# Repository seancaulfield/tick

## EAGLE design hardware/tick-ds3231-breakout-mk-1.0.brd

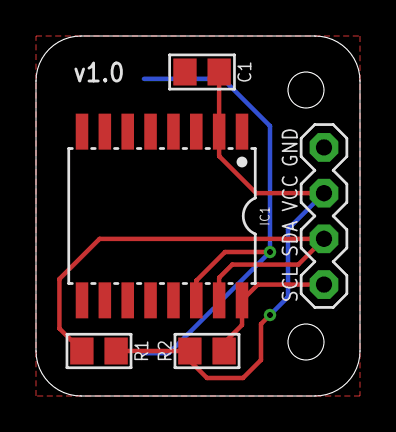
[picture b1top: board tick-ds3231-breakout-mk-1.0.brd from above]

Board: 2 copper layers, 18.0 x 20.0 mm, 7 parts (1 on the bottom side), 5 nets.

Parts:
C1: 100n; C0805
FRAME1: FRAME-LETTERNO_PACKAGE; DUMMY
I2C: M04-I2CPTH-0.1IN-CENTERED; 1X04-PTH-VERT-I2C-CENTERED
IC1: DS3231; SO16W
R1, R2: 4.7k; R0805
RTC_BATT: CR1225; BATTCON_12MM_SMD

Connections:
GND: C1.2, I2C.GND, IC1.5, IC1.6, IC1.7, IC1.8, IC1.9, IC1.10, IC1.11, IC1.12, IC1.13, RTC_BATT.-
SCL: I2C.SCL, IC1.16, R2.2
SDA: I2C.SDA, IC1.15, R1.2
VBAT: IC1.14, RTC_BATT.+@1, RTC_BATT.+@2
VCC: C1.1, I2C.VCC, IC1.2, R1.1, R2.1

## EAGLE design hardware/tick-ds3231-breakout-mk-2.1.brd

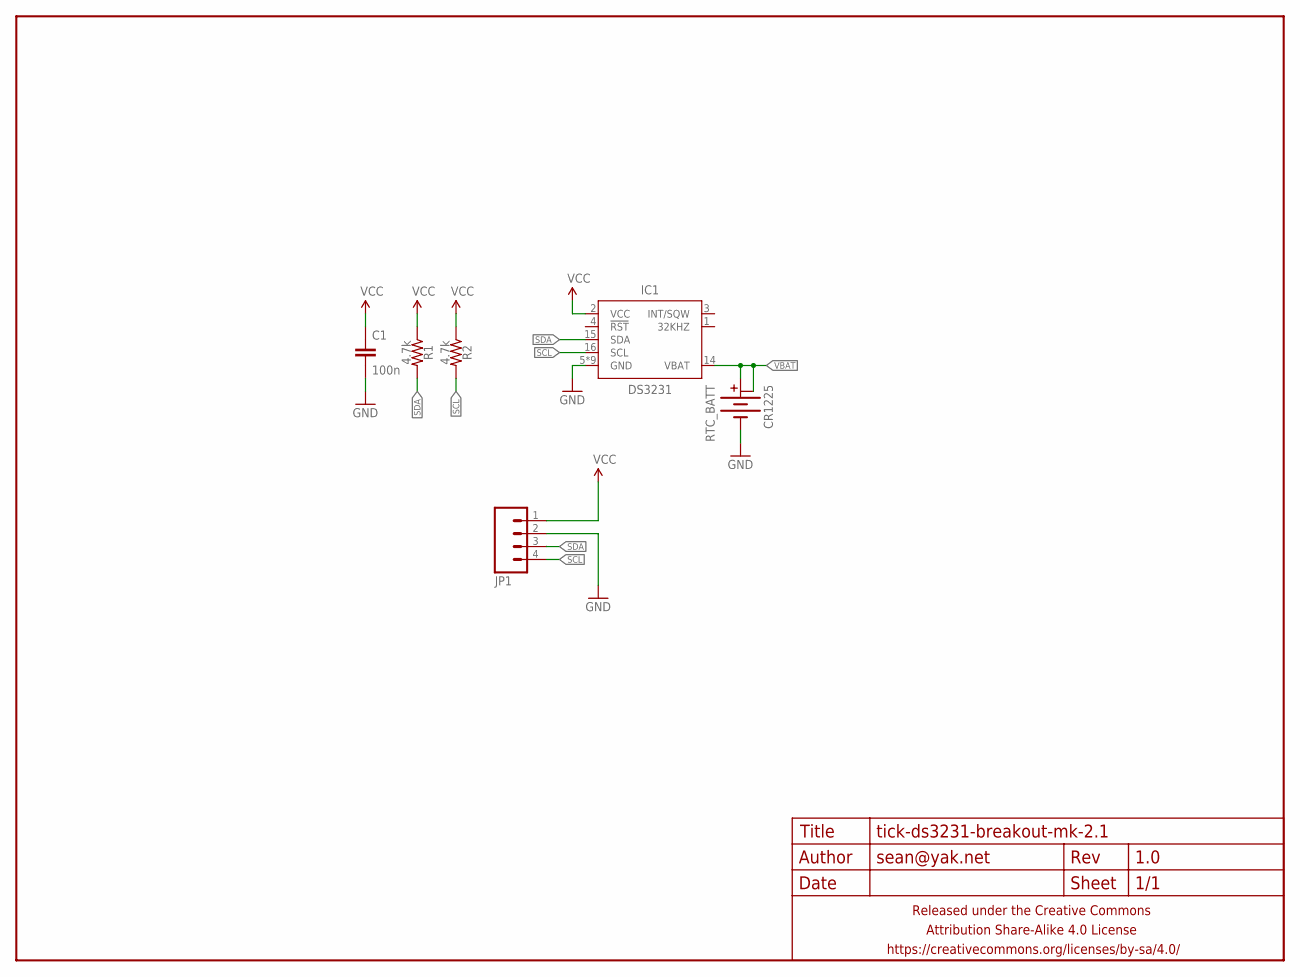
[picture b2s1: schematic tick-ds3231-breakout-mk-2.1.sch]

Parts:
C1: 100n; C0805
FRAME1: FRAME-LETTERNO_PACKAGE; DUMMY
IC1: DS3231; SO16W
JP1: M04PTH; 1X04-PTH-VERT
R1, R2: 4.7k; R0805
RTC_BATT: CR1225; BATTCON_12MM_SMD

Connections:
GND: C1.2, IC1.5 (GND), IC1.6 (GND), IC1.7 (GND), IC1.8 (GND), IC1.9 (GND), IC1.10 (GND), IC1.11 (GND), IC1.12 (GND), IC1.13 (GND), JP1.2, RTC_BATT.-
SCL: IC1.16 (SCL), JP1.4, R2.2
SDA: IC1.15 (SDA), JP1.3, R1.2
VBAT: IC1.14 (VBAT), RTC_BATT.+@1 (+), RTC_BATT.+@2 (+1)
VCC: C1.1, IC1.2 (VCC), JP1.1, R1.1, R2.1

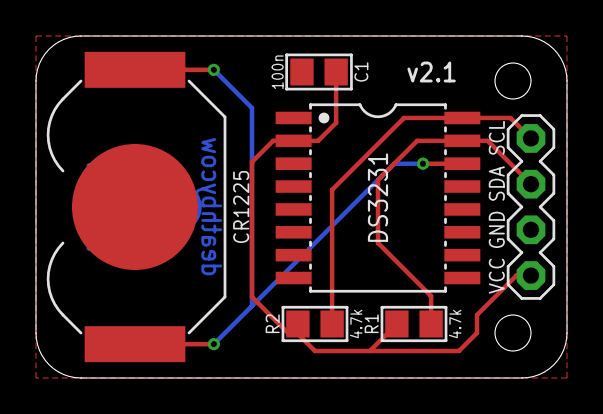
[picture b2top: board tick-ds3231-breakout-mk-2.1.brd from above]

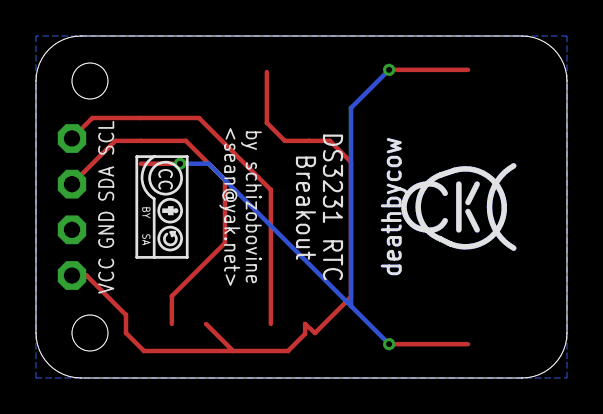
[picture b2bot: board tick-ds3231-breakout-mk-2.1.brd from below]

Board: 2 copper layers, 29.5 x 19.0 mm, 9 parts (2 on the bottom side), 5 nets.

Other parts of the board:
U$1: COW_SMALL_METAL
U$2: CC-BY-SA-4.0-NO-URL

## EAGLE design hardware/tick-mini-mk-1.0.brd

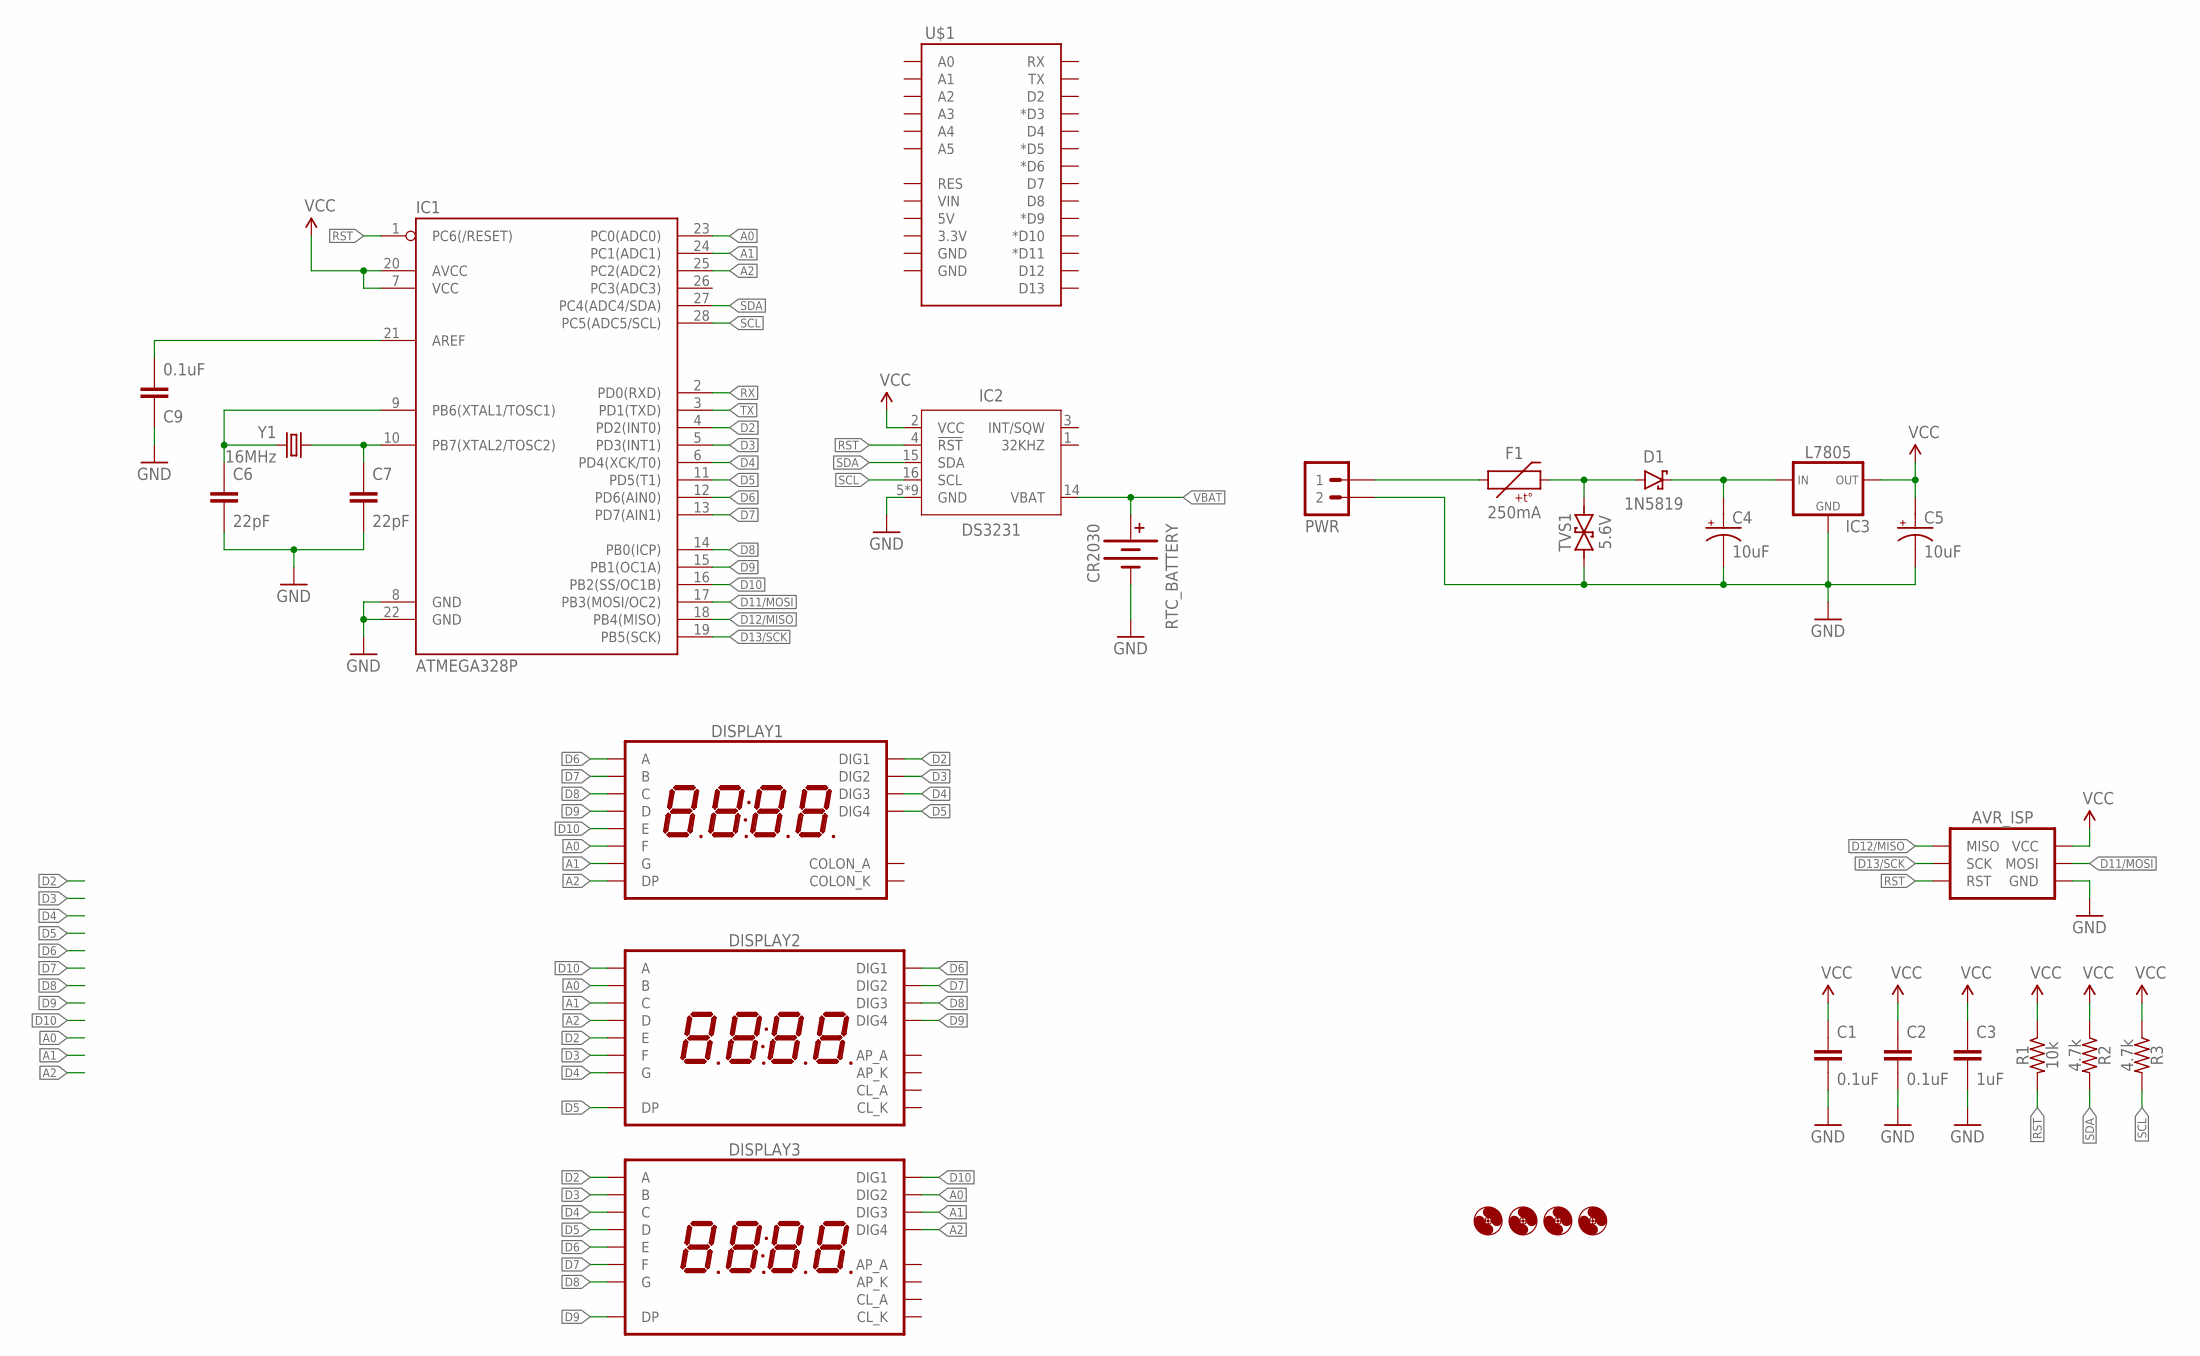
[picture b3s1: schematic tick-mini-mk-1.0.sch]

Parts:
AVR_ISP: AVR_SPI_PRG_6PTH; 2X3
C1, C2, C9: 0.1uF; C025-024X044
C3: 1uF; C025-024X044
C4, C5: 10uF; E2-5
C6, C7: 22pF; C025-024X044
D1: 1N5819; DIODE-10.16MM
DISPLAY1: 7SEG_4DIGIT_COLON14.2MM-CC; 7SEG_4DIG_0.56IN_14MM_ADAFRUIT
DISPLAY2, DISPLAY3: 7SEG_4DIGIT_COLON_APOS; 7SEG_4DIG_10MM
F1: 250mA; PTC-PTH-5.08MM
H1, H2, H3, H4: HOLE#2; HOLE-#2
IC1: ATMEGA328P; DIL28-3
IC2: DS3231; SO16W
IC3: L7805; TO-92-AMMO
PWR: M02JST-PTH-VERT; JST-2-PH-VERT-PTH
R1: 10k; RESISTOR-AXIAL-PTH-7.62MM
R2, R3: 4.7k; RESISTOR-AXIAL-PTH-6.35MM
RTC_BATTERY: CR2030; BATTCON_12MM
TVS1: 5.6V; DO-41-TVS-BI-10.16MM
U$1: ARDUINO_SHIELD_SMALLER; ARDUINO_SHIELD_NOOUTLINE_INSIDE_SMALLER
Y1: 16MHz; HC49U-V

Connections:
A0: DISPLAY1.P$12 (F), DISPLAY2.16 (B), DISPLAY3.2 (DIG2), IC1.23 (PC0(ADC0))
A1: DISPLAY1.P$5 (G), DISPLAY2.13 (C), DISPLAY3.6 (DIG3), IC1.24 (PC1(ADC1))
A2: DISPLAY1.P$3 (DP), DISPLAY2.3 (D), DISPLAY3.8 (DIG4), IC1.25 (PC2(ADC2))
D2: DISPLAY1.P$14 (DIG1), DISPLAY2.5 (E), DISPLAY3.14 (A), IC1.4 (PD2(INT0))
D3: DISPLAY1.P$11 (DIG2), DISPLAY2.11 (F), DISPLAY3.16 (B), IC1.5 (PD3(INT1))
D4: DISPLAY1.P$10 (DIG3), DISPLAY2.15 (G), DISPLAY3.13 (C), IC1.6 (PD4(XCK/T0))
D5: DISPLAY1.P$6 (DIG4), DISPLAY2.7 (DP), DISPLAY3.3 (D), IC1.11 (PD5(T1))
D6: DISPLAY1.P$13 (A), DISPLAY2.1 (DIG1), DISPLAY3.5 (E), IC1.12 (PD6(AIN0))
D7: DISPLAY1.P$9 (B), DISPLAY2.2 (DIG2), DISPLAY3.11 (F), IC1.13 (PD7(AIN1))
D8: DISPLAY1.P$4 (C), DISPLAY2.6 (DIG3), DISPLAY3.15 (G), IC1.14 (PB0(ICP))
D9: DISPLAY1.P$2 (D), DISPLAY2.8 (DIG4), DISPLAY3.7 (DP), IC1.15 (PB1(OC1A))
D10: DISPLAY1.P$1 (E), DISPLAY2.14 (A), DISPLAY3.1 (DIG1), IC1.16 (PB2(SS/OC1B))
D11/MOSI: AVR_ISP.4 (MOSI), IC1.17 (PB3(MOSI/OC2))
D12/MISO: AVR_ISP.1 (MISO), IC1.18 (PB4(MISO))
D13/SCK: AVR_ISP.3 (SCK), IC1.19 (PB5(SCK))
GND: AVR_ISP.6 (GND), C1.2, C2.2, C3.2, C4.-, C5.-, C6.2, C7.2, C9.1, IC1.8 (GND), IC1.22 (GND), IC2.5 (GND), IC2.6 (GND), IC2.7 (GND), IC2.8 (GND), IC2.9 (GND), IC2.10 (GND), IC2.11 (GND), IC2.12 (GND), IC2.13 (GND), IC3.2 (GND), PWR.2, RTC_BATTERY.GND (-), TVS1.P$1 (1)
unnamed: C9.2, IC1.21 (AREF)
unnamed: D1.A, F1.P$2 (2), TVS1.P$2 (2)
unnamed: C6.1, IC1.9 (PB6(XTAL1/TOSC1)), Y1.2
unnamed: F1.P$1 (1), PWR.1
unnamed: C4.+, D1.C, IC3.1 (IN)
unnamed: C7.1, IC1.10 (PB7(XTAL2/TOSC2)), Y1.1
RST: AVR_ISP.5 (RST), IC1.1 (PC6(/RESET)), IC2.4 (!RST), R1.P$2 (2)
RX: IC1.2 (PD0(RXD))
SCL: IC1.28 (PC5(ADC5/SCL)), IC2.16 (SCL), R3.P$2 (2)
SDA: IC1.27 (PC4(ADC4/SDA)), IC2.15 (SDA), R2.P$2 (2)
TX: IC1.3 (PD1(TXD))
VBAT: IC2.14 (VBAT), RTC_BATTERY.PWR@1 (+)
VCC: AVR_ISP.2 (VCC), C1.1, C2.1, C3.1, C5.+, IC1.7 (VCC), IC1.20 (AVCC), IC2.2 (VCC), IC3.3 (OUT), R1.P$1 (1), R2.P$1 (1), R3.P$1 (1)

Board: 2 copper layers, 29 parts (5 on the bottom side), 27 nets, no tracks yet.

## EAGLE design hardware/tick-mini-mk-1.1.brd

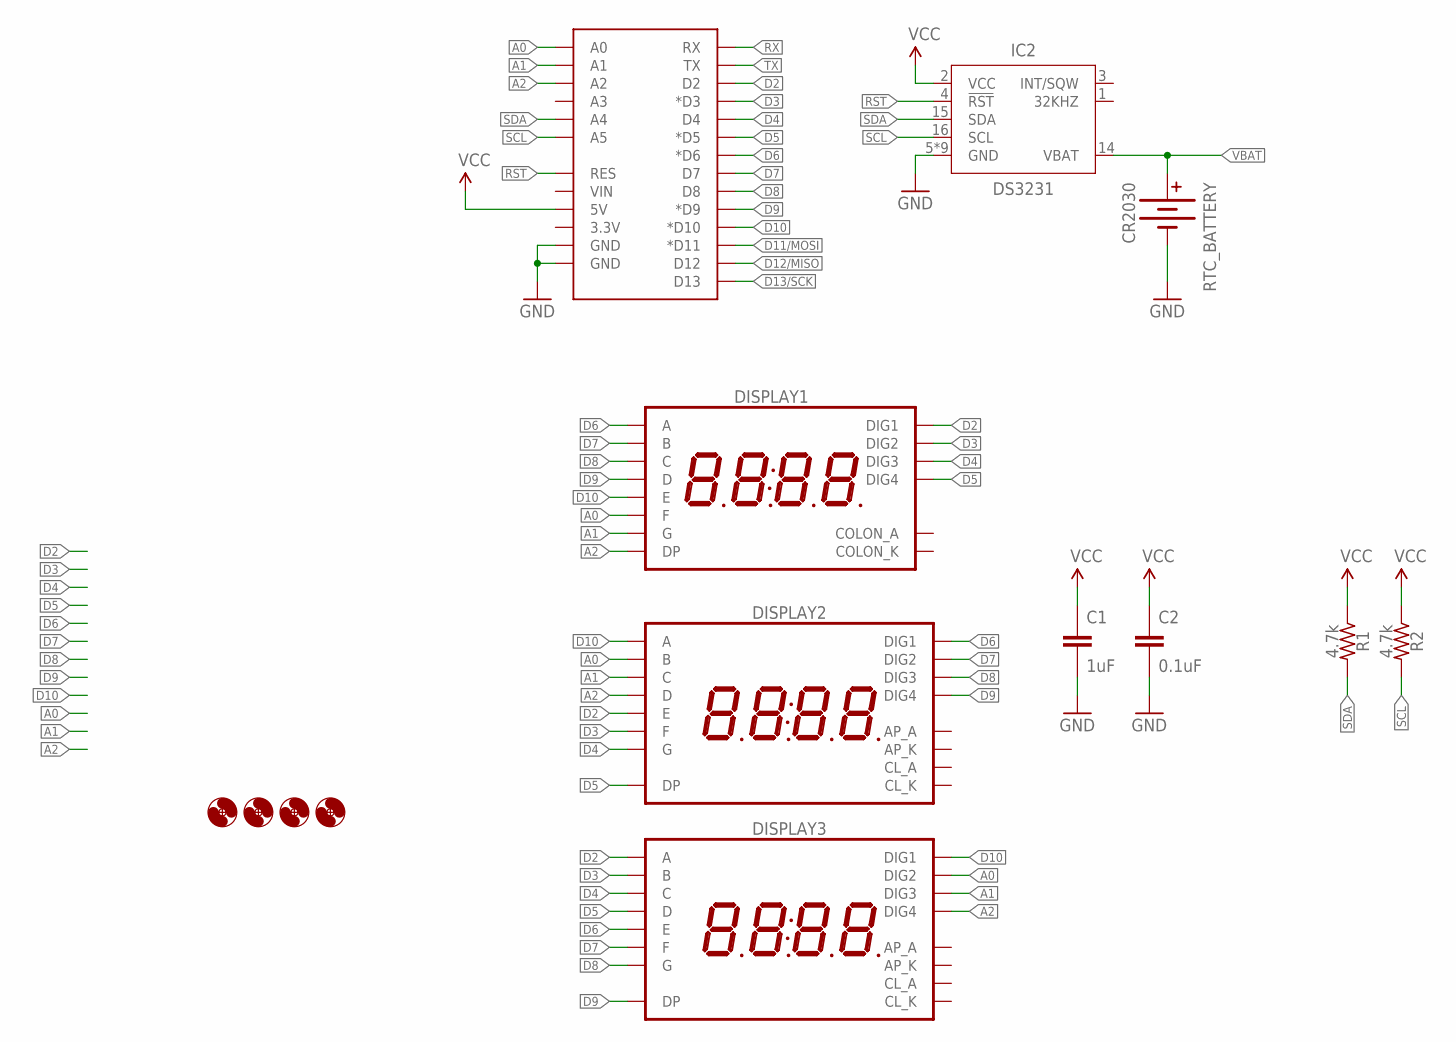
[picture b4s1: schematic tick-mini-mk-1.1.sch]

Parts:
C1: 1uF; C025-024X044
C2: 0.1uF; C025-024X044
DISPLAY1: 7SEG_4DIGIT_COLON14.2MM-CC-NS; 7SEG_4DIG_NS
DISPLAY2, DISPLAY3: 7SEG_4DIGIT_COLON_APOS; 7SEG_4DIG_10MM
H1, H2, H3, H4: HOLE#2; HOLE-#2
IC2: DS3231; SO16W
R1, R2: 4.7k; RESISTOR-AXIAL-PTH-6.35MM
RTC_BATTERY: CR2030; BATTCON_20MM_MINE
U$1: ARDUINO_SHIELD_SMALLER; ARDUINO_SHIELD_NOOUTLINE_INSIDE_SMALLER

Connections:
A0: DISPLAY1.P$12 (F), DISPLAY2.16 (B), DISPLAY3.2 (DIG2), U$1.A0
A1: DISPLAY1.P$5 (G), DISPLAY2.13 (C), DISPLAY3.6 (DIG3), U$1.A1
A2: DISPLAY1.P$3 (DP), DISPLAY2.3 (D), DISPLAY3.8 (DIG4), U$1.A2
D2: DISPLAY1.P$14 (DIG1), DISPLAY2.5 (E), DISPLAY3.14 (A), U$1.D2
D3: DISPLAY1.P$11 (DIG2), DISPLAY2.11 (F), DISPLAY3.16 (B), U$1.D3 (*D3)
D4: DISPLAY1.P$10 (DIG3), DISPLAY2.15 (G), DISPLAY3.13 (C), U$1.D4
D5: DISPLAY1.P$6 (DIG4), DISPLAY2.7 (DP), DISPLAY3.3 (D), U$1.D5 (*D5)
D6: DISPLAY1.P$13 (A), DISPLAY2.1 (DIG1), DISPLAY3.5 (E), U$1.D6 (*D6)
D7: DISPLAY1.P$9 (B), DISPLAY2.2 (DIG2), DISPLAY3.11 (F), U$1.D7
D8: DISPLAY1.P$4 (C), DISPLAY2.6 (DIG3), DISPLAY3.15 (G), U$1.D8
D9: DISPLAY1.P$2 (D), DISPLAY2.8 (DIG4), DISPLAY3.7 (DP), U$1.D9 (*D9)
D10: DISPLAY1.P$1 (E), DISPLAY2.14 (A), DISPLAY3.1 (DIG1), U$1.D10 (*D10)
D11/MOSI: U$1.D11 (*D11)
D12/MISO: U$1.D12
D13/SCK: U$1.D13
GND: C1.2, C2.2, IC2.5 (GND), IC2.6 (GND), IC2.7 (GND), IC2.8 (GND), IC2.9 (GND), IC2.10 (GND), IC2.11 (GND), IC2.12 (GND), IC2.13 (GND), RTC_BATTERY.BOTTOM (-), U$1.GND@0 (GND), U$1.GND@1 (GND)
RST: IC2.4 (!RST), U$1.RES
RX: U$1.RX
SCL: IC2.16 (SCL), R2.P$2 (2), U$1.A5
SDA: IC2.15 (SDA), R1.P$2 (2), U$1.A4
TX: U$1.TX
VBAT: IC2.14 (VBAT), RTC_BATTERY.TOP@1 (+), RTC_BATTERY.TOP@2 (+)
VCC: C1.1, C2.1, IC2.2 (VCC), R1.P$1 (1), R2.P$1 (1), U$1.5V

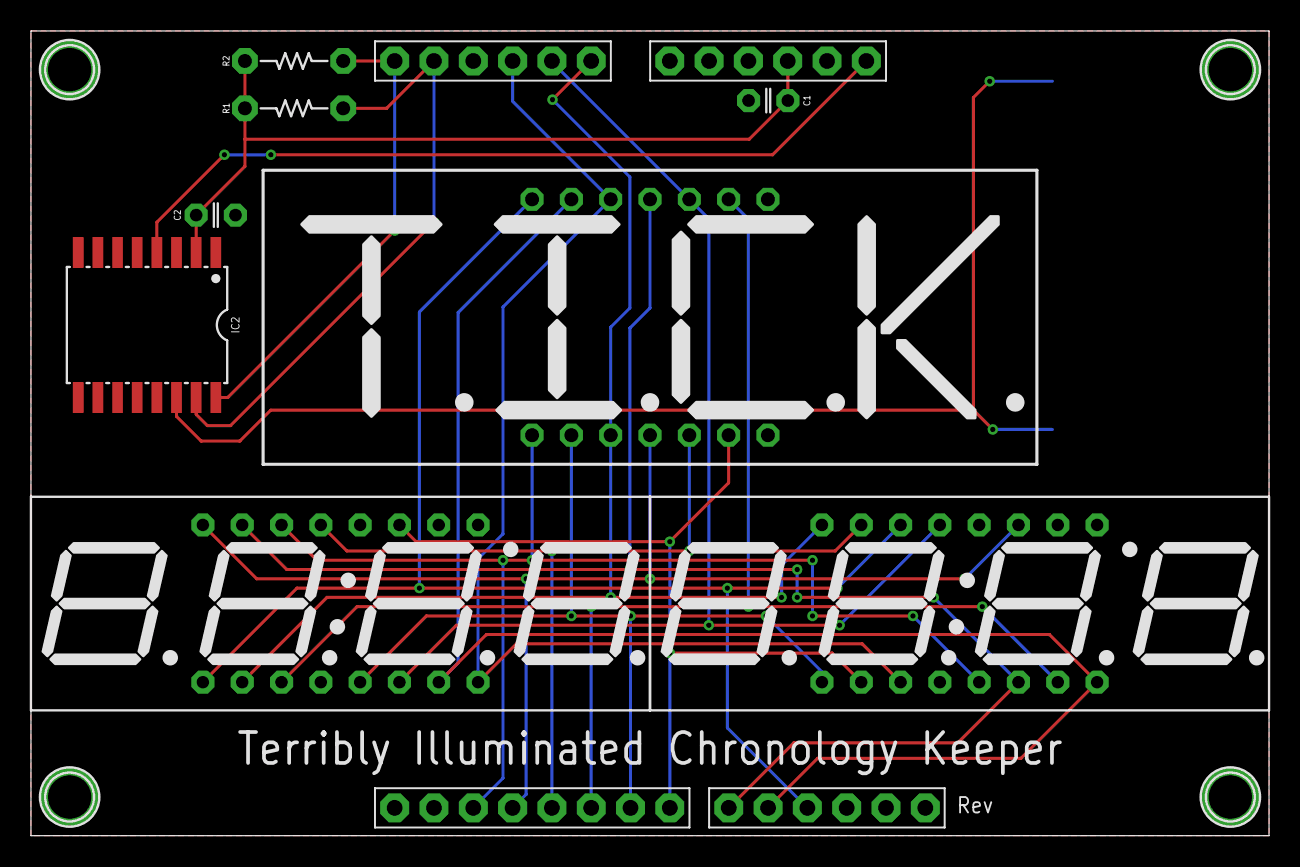
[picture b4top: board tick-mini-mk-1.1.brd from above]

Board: 2 copper layers, 80.0 x 52.0 mm, 15 parts (1 on the bottom side), 18 nets.

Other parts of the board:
U$2: TICK_SYMBOL_0.56

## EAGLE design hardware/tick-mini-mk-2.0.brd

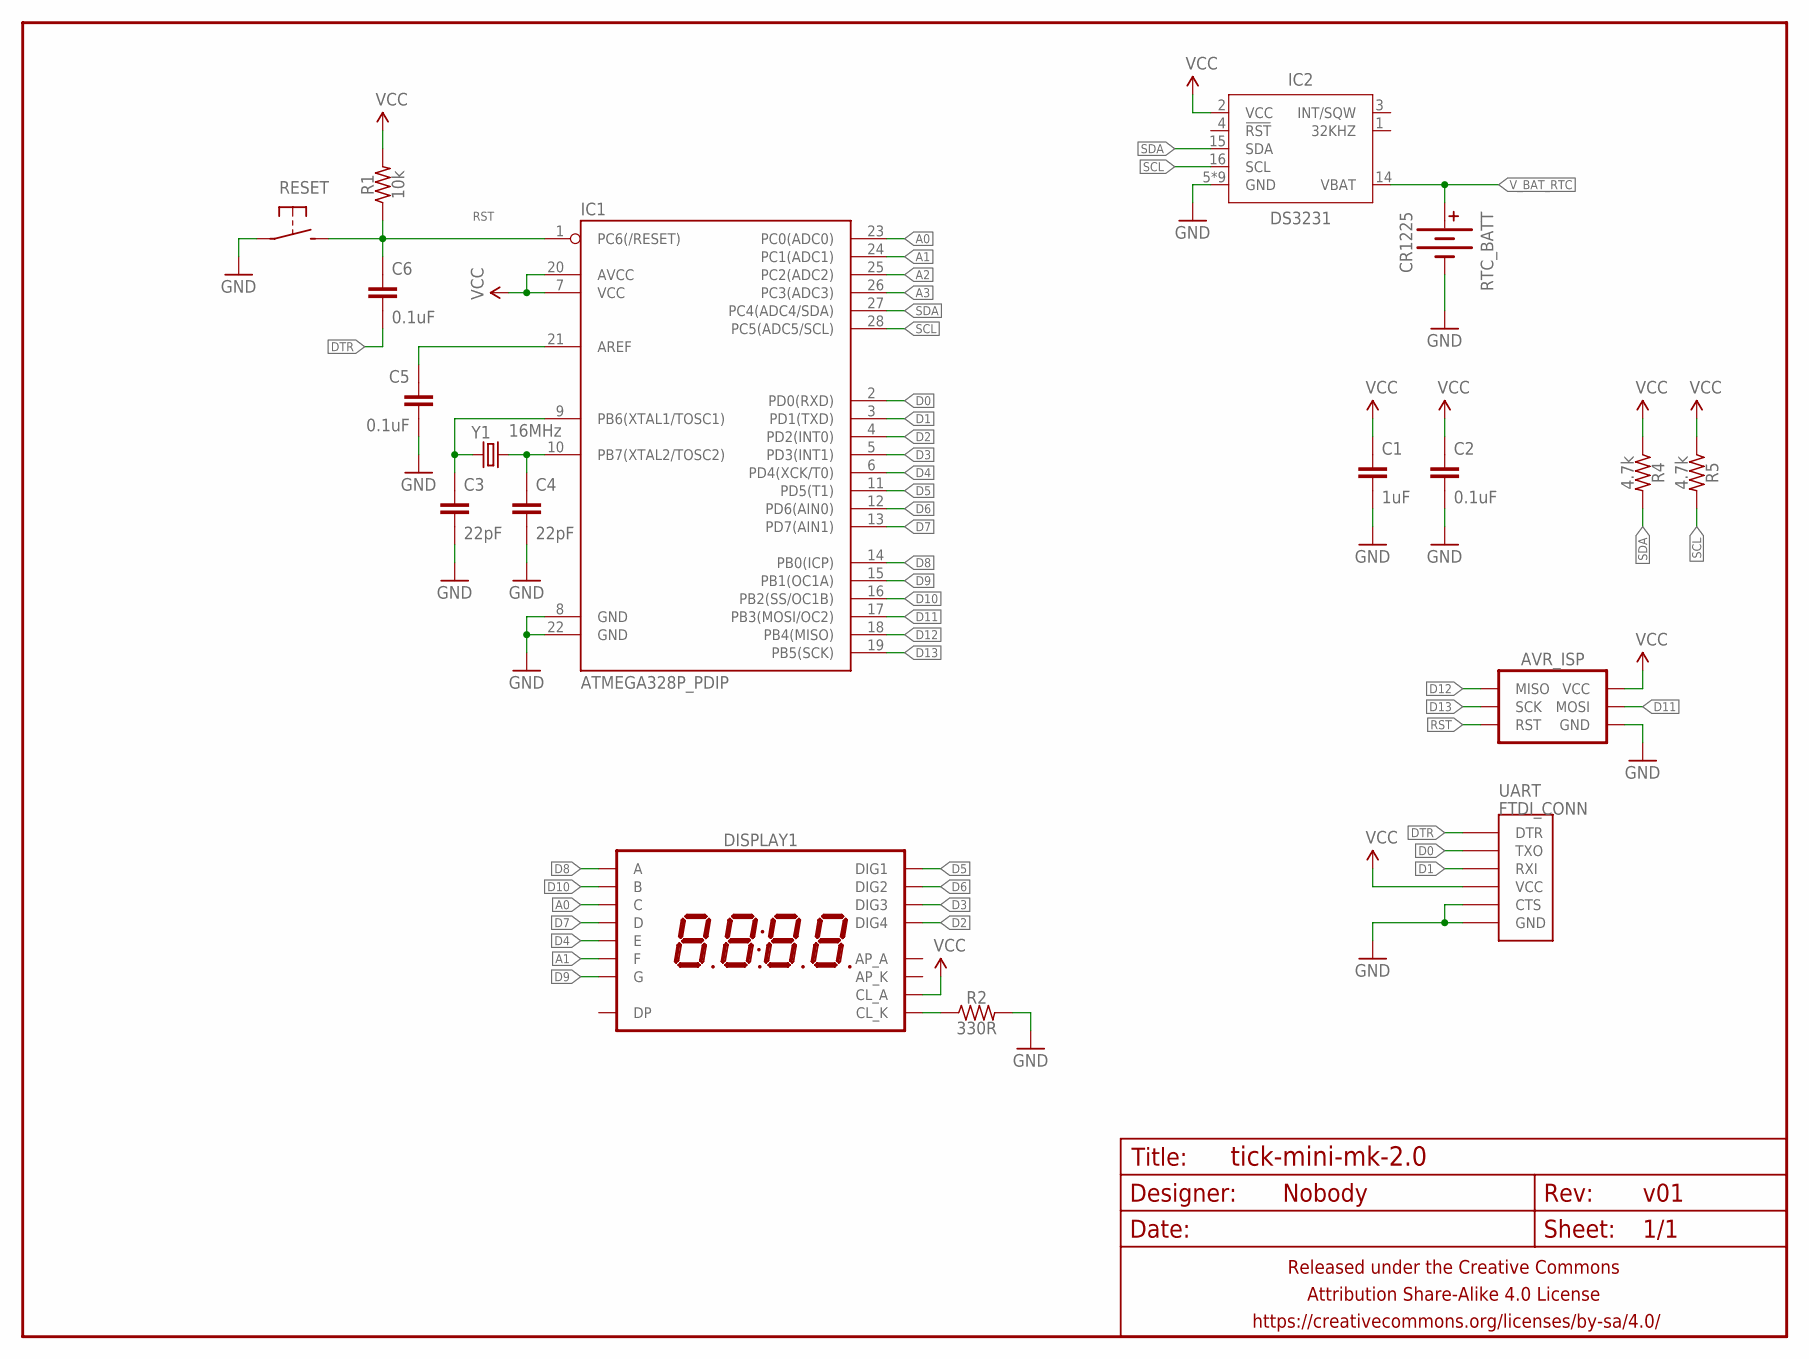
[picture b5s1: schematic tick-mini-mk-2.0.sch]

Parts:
AVR_ISP: AVR_SPI_PRG_6PTH; 2X3
C1: 1uF; C025-024X044
C2, C5, C6: 0.1uF; C025-024X044
C3, C4: 22pF; C025-024X044
DISPLAY1: 7SEG_4DIGIT_COLON_APOS; 7SEG_4DIG_10MM
FRAME1: FRAME-LETTERNO_PACKAGE; DUMMY
IC1: ATMEGA328P_PDIP; DIL28-3
IC2: DS3231; SO16W
R1: 10k; RESISTOR-AXIAL-PTH-6.35MM
R2: 330R; RESISTOR-AXIAL-PTH-6.35MM
R4, R5: 4.7k; RESISTOR-AXIAL-PTH-6.35MM
RESET: SPST-NO-TACT6MM-PTH-SMALL-PADS; DTS-6-SMALL-PADS
RTC_BATT: CR1225; BATTCON_12MM_PTH_TOPLOAD
UART: FTDI_CONN
Y1: 16MHz; HC49U-V

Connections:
A0: DISPLAY1.13 (C), IC1.23 (PC0(ADC0))
A1: DISPLAY1.11 (F), IC1.24 (PC1(ADC1))
A2: IC1.25 (PC2(ADC2))
A3: IC1.26 (PC3(ADC3))
D0: IC1.2 (PD0(RXD)), UART.TXO
D1: IC1.3 (PD1(TXD)), UART.RXI
D2: DISPLAY1.8 (DIG4), IC1.4 (PD2(INT0))
D3: DISPLAY1.6 (DIG3), IC1.5 (PD3(INT1))
D4: DISPLAY1.5 (E), IC1.6 (PD4(XCK/T0))
D5: DISPLAY1.1 (DIG1), IC1.11 (PD5(T1))
D6: DISPLAY1.2 (DIG2), IC1.12 (PD6(AIN0))
D7: DISPLAY1.3 (D), IC1.13 (PD7(AIN1))
D8: DISPLAY1.14 (A), IC1.14 (PB0(ICP))
D9: DISPLAY1.15 (G), IC1.15 (PB1(OC1A))
D10: DISPLAY1.16 (B), IC1.16 (PB2(SS/OC1B))
D11: AVR_ISP.4 (MOSI), IC1.17 (PB3(MOSI/OC2))
D12: AVR_ISP.1 (MISO), IC1.18 (PB4(MISO))
D13: AVR_ISP.3 (SCK), IC1.19 (PB5(SCK))
DTR: C6.2, UART.DTR
GND: AVR_ISP.6 (GND), C1.2, C2.2, C3.2, C4.2, C5.2, IC1.8 (GND), IC1.22 (GND), IC2.5 (GND), IC2.6 (GND), IC2.7 (GND), IC2.8 (GND), IC2.9 (GND), IC2.10 (GND), IC2.11 (GND), IC2.12 (GND), IC2.13 (GND), R2.P$2 (2), RESET.1, RESET.2 (1), RTC_BATT.-, UART.CTS, UART.GND
unnamed: C4.1, IC1.10 (PB7(XTAL2/TOSC2)), Y1.2
unnamed: C3.1, IC1.9 (PB6(XTAL1/TOSC1)), Y1.1
unnamed: C5.1, IC1.21 (AREF)
unnamed: DISPLAY1.12 (CL_K), R2.P$1 (1)
RST: AVR_ISP.5 (RST), C6.1, IC1.1 (PC6(/RESET)), R1.P$1 (1), RESET.3 (2), RESET.4 (2)
SCL: IC1.28 (PC5(ADC5/SCL)), IC2.16 (SCL), R5.P$2 (2)
SDA: IC1.27 (PC4(ADC4/SDA)), IC2.15 (SDA), R4.P$2 (2)
VCC: AVR_ISP.2 (VCC), C1.1, C2.1, DISPLAY1.4 (CL_A), IC1.7 (VCC), IC1.20 (AVCC), IC2.2 (VCC), R1.P$2 (2), R4.P$1 (1), R5.P$1 (1), UART.VCC
V_BAT_RTC: IC2.14 (VBAT), RTC_BATT.+

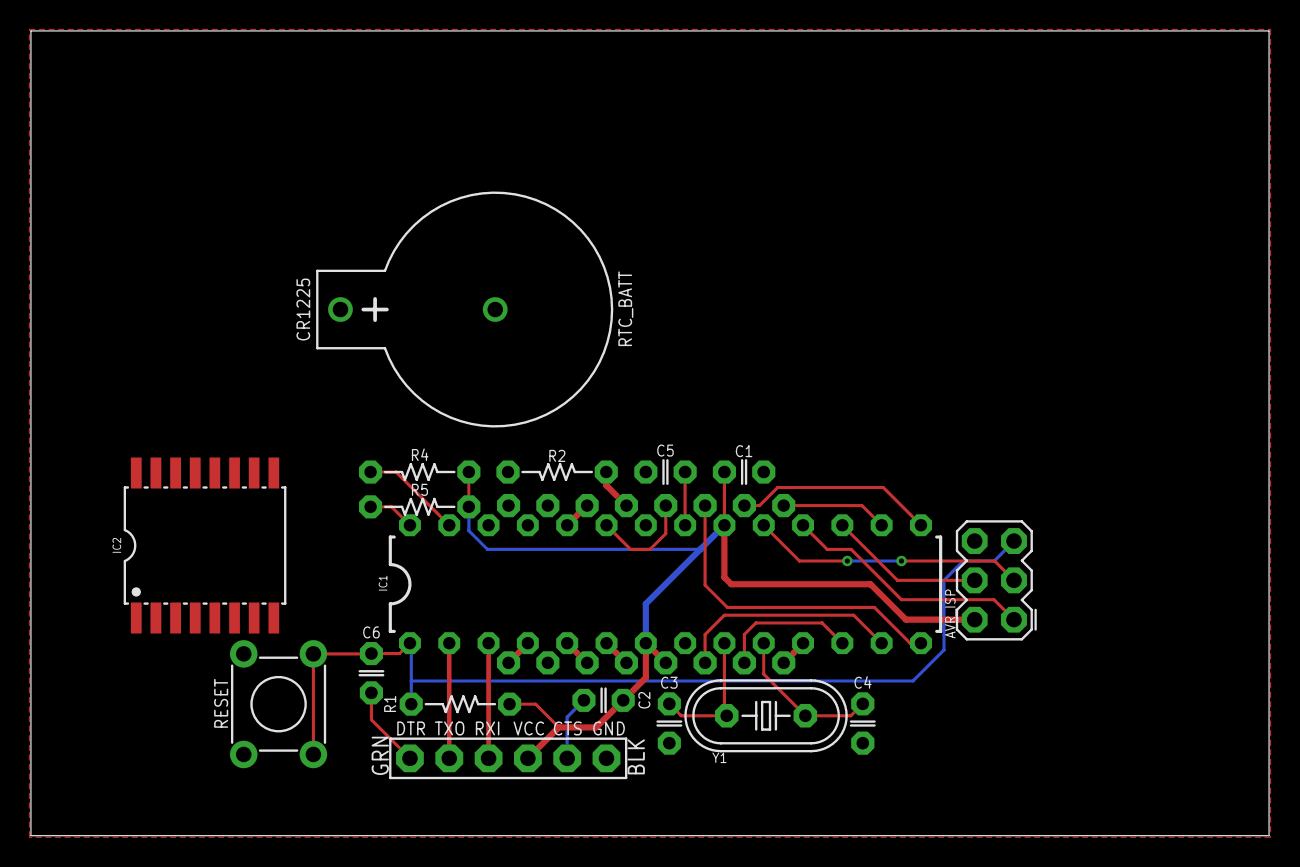
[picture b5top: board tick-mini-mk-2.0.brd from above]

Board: 2 copper layers, 80.0 x 52.0 mm, 19 parts (1 on the bottom side), 27 nets.

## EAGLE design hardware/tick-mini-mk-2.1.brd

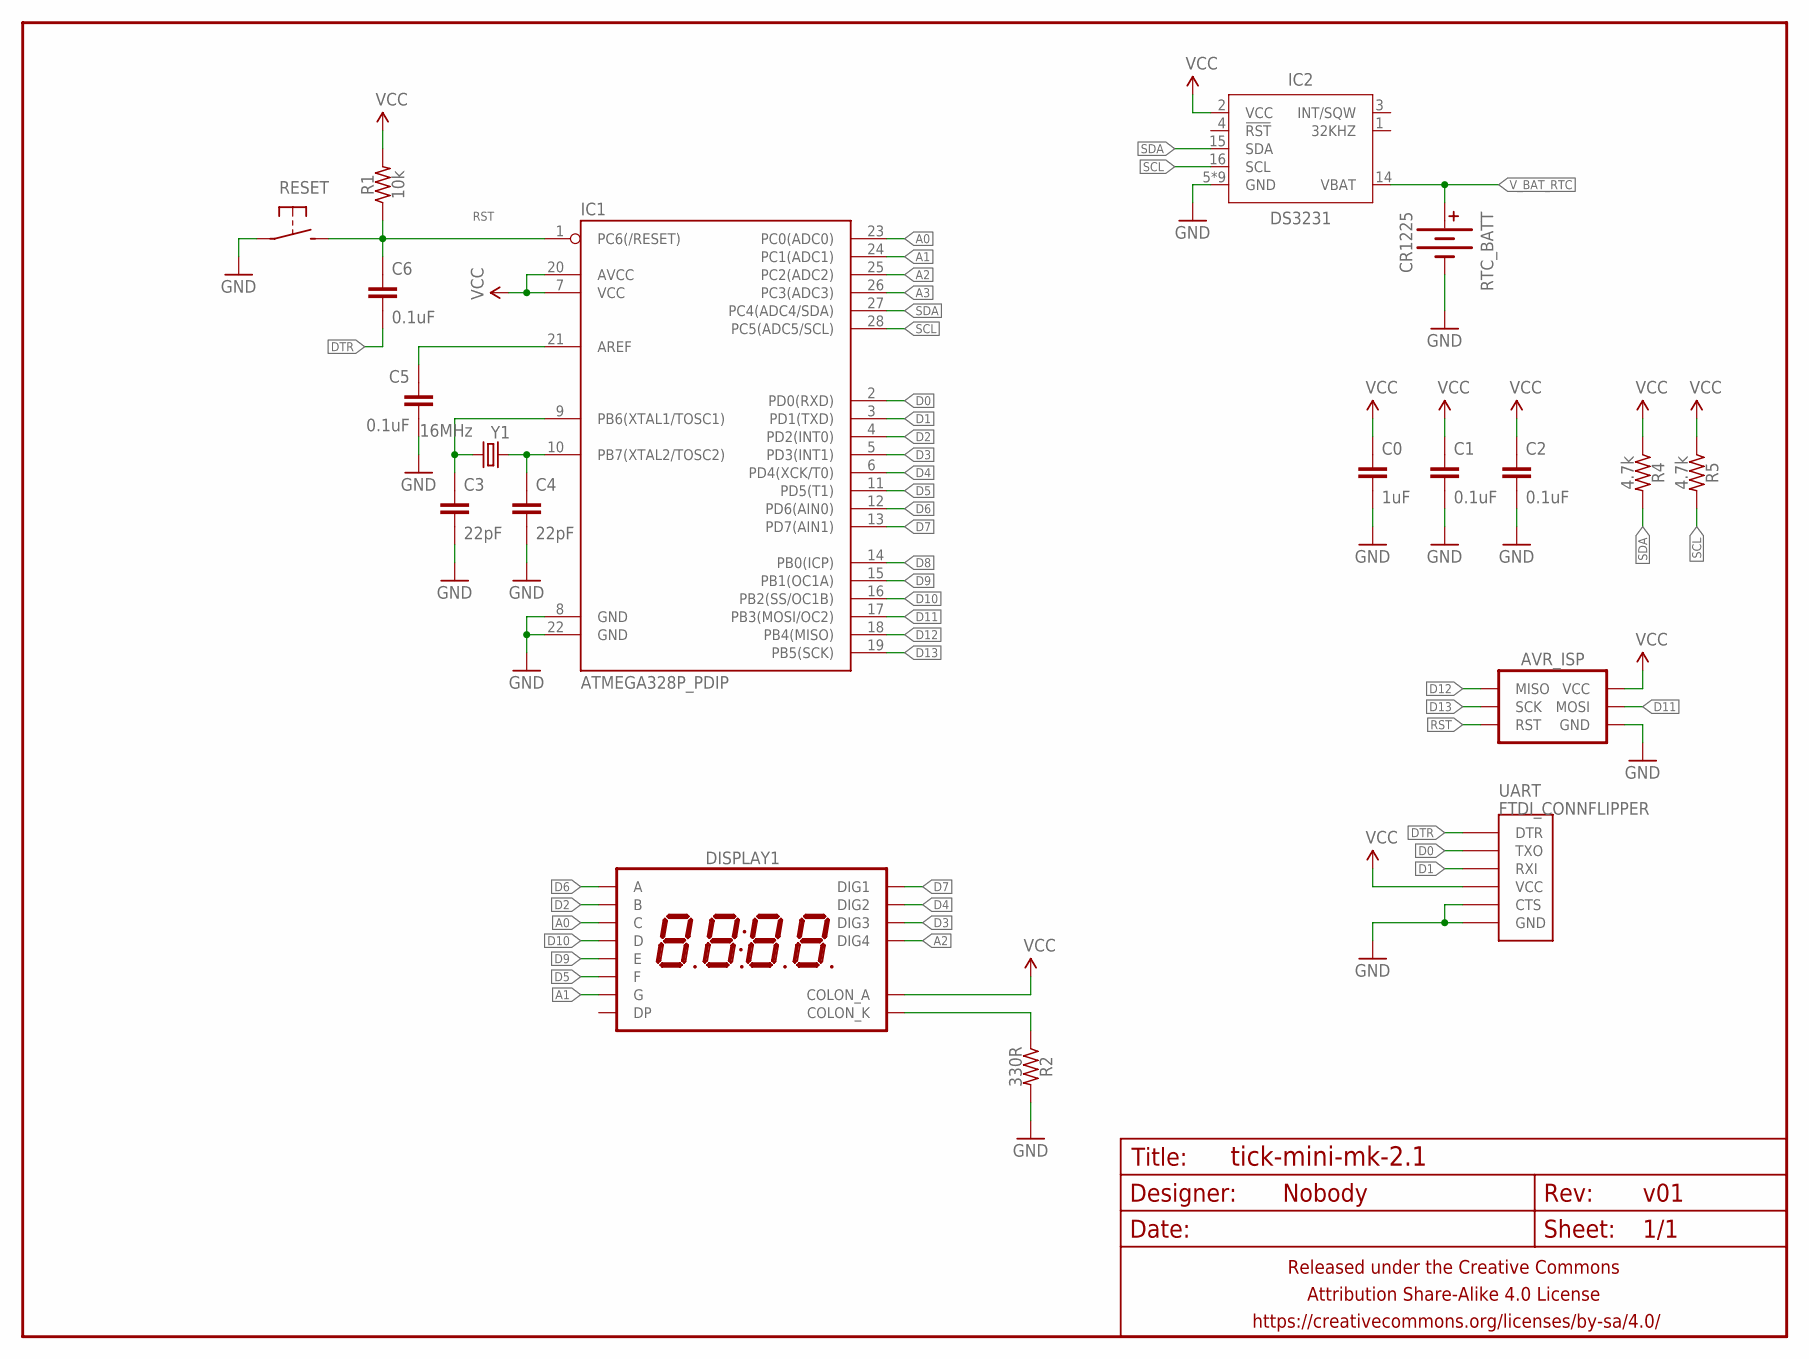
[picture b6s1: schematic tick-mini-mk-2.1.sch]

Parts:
AVR_ISP: AVR_SPI_PRG_6INLINE; AVR_MINI_PROG
C0: 1uF; C025-024X044
C1, C2, C5, C6: 0.1uF; C025-024X044
C3, C4: 22pF; C025-024X044
DISPLAY1: 7SEG_4DIGIT_COLON14.2MM-CC-NS; 7SEG_4DIG_NS
FRAME1: FRAME-LETTERNO_PACKAGE; DUMMY
IC1: ATMEGA328P_PDIP; DIL28-3
IC2: DS3231; SO16W
R1: 10k; RESISTOR-AXIAL-PTH-7.62MM
R2: 330R; RESISTOR-AXIAL-PTH-7.62MM
R4, R5: 4.7k; RESISTOR-AXIAL-PTH-7.62MM
RESET: SPST-NO-TACT3MM-RA; TACTILE-PTH-SIDE
RTC_BATT: CR1225; BATTCON_12MM
UART: FTDI_CONNFLIPPER; FTDI_CONN_FLIP
Y1: 16MHz; HC49U-V

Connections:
A0: DISPLAY1.P$4 (C), IC1.23 (PC0(ADC0))
A1: DISPLAY1.P$5 (G), IC1.24 (PC1(ADC1))
A2: DISPLAY1.P$6 (DIG4), IC1.25 (PC2(ADC2))
A3: IC1.26 (PC3(ADC3))
D0: IC1.2 (PD0(RXD)), UART.TXO
D1: IC1.3 (PD1(TXD)), UART.RXI
D2: DISPLAY1.P$9 (B), IC1.4 (PD2(INT0))
D3: DISPLAY1.P$10 (DIG3), IC1.5 (PD3(INT1))
D4: DISPLAY1.P$11 (DIG2), IC1.6 (PD4(XCK/T0))
D5: DISPLAY1.P$12 (F), IC1.11 (PD5(T1))
D6: DISPLAY1.P$13 (A), IC1.12 (PD6(AIN0))
D7: DISPLAY1.P$14 (DIG1), IC1.13 (PD7(AIN1))
D8: IC1.14 (PB0(ICP))
D9: DISPLAY1.P$1 (E), IC1.15 (PB1(OC1A))
D10: DISPLAY1.P$2 (D), IC1.16 (PB2(SS/OC1B))
D11: AVR_ISP.4 (MOSI), IC1.17 (PB3(MOSI/OC2))
D12: AVR_ISP.1 (MISO), IC1.18 (PB4(MISO))
D13: AVR_ISP.3 (SCK), IC1.19 (PB5(SCK))
DTR: C6.2, UART.DTR
GND: AVR_ISP.6 (GND), C0.2, C1.2, C2.2, C3.2, C4.2, C5.2, IC1.8 (GND), IC1.22 (GND), IC2.5 (GND), IC2.6 (GND), IC2.7 (GND), IC2.8 (GND), IC2.9 (GND), IC2.10 (GND), IC2.11 (GND), IC2.12 (GND), IC2.13 (GND), R2.P$2 (2), RESET.1, RTC_BATT.GND (-), UART.CTS, UART.GND
unnamed: C4.1, IC1.10 (PB7(XTAL2/TOSC2)), Y1.1
unnamed: C3.1, IC1.9 (PB6(XTAL1/TOSC1)), Y1.2
unnamed: C5.1, IC1.21 (AREF)
unnamed: DISPLAY1.P$7 (COLON_K), R2.P$1 (1)
RST: AVR_ISP.5 (RST), C6.1, IC1.1 (PC6(/RESET)), R1.P$1 (1), RESET.2
SCL: IC1.28 (PC5(ADC5/SCL)), IC2.16 (SCL), R5.P$2 (2)
SDA: IC1.27 (PC4(ADC4/SDA)), IC2.15 (SDA), R4.P$2 (2)
VCC: AVR_ISP.2 (VCC), C0.1, C1.1, C2.1, DISPLAY1.P$8 (COLON_A), IC1.7 (VCC), IC1.20 (AVCC), IC2.2 (VCC), R1.P$2 (2), R4.P$1 (1), R5.P$1 (1), UART.VCC
V_BAT_RTC: IC2.14 (VBAT), RTC_BATT.PWR@1 (+)

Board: 2 copper layers, 20 parts (5 on the bottom side), 27 nets, no tracks yet.

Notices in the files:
parts and their libraries:
A_butts: Released under the Creative Commons Attribution Share-Alike 4.0 License
A_butts: https://creativecommons.org/licenses/by-sa/4.0
A_butts: Released under the Creative Commons
